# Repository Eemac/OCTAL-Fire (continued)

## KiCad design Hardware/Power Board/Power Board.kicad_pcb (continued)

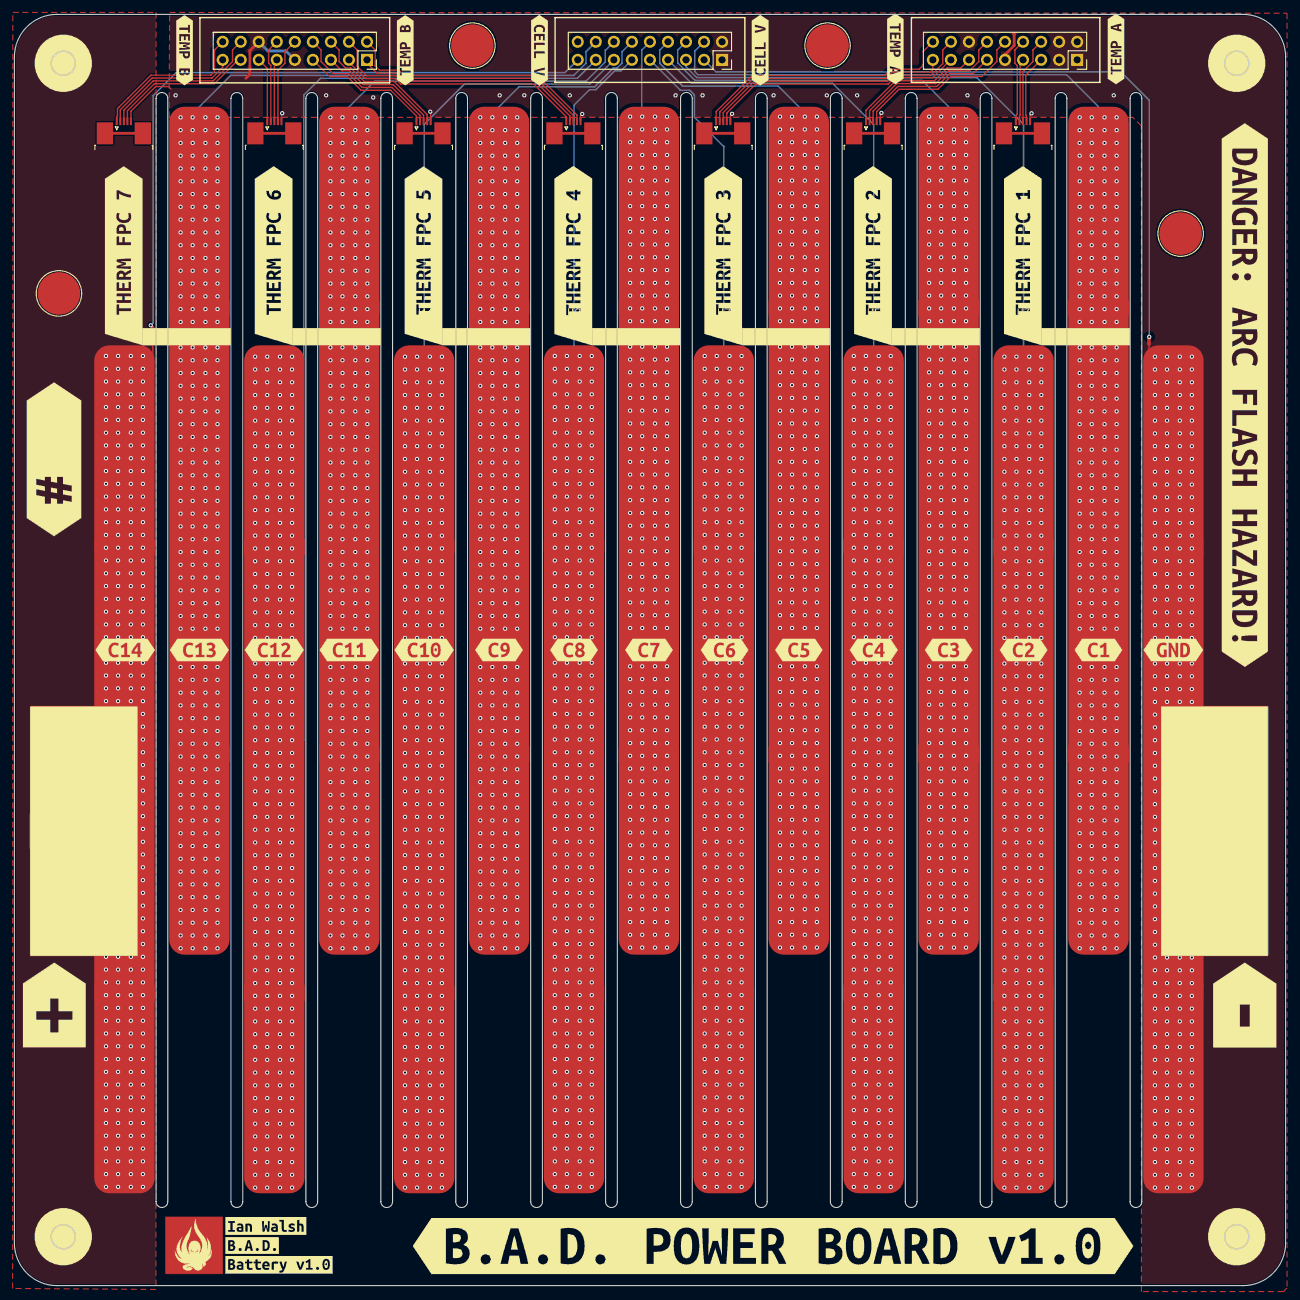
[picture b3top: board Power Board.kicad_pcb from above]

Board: 4 copper layers, 179.0 x 179.0 mm, 67 parts (0 on the bottom side), 45 nets.

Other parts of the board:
kibuzzard-68FE6C25: G***; kibuzzard-68FE6C25
kibuzzard-68FE8BAD: G***; kibuzzard-68FE8BAD
kibuzzard-68FE8C3A: G***; kibuzzard-68FE8C3A
kibuzzard-68FE8C6B: G***; kibuzzard-68FE8C6B
kibuzzard-68FE8C6F: G***; kibuzzard-68FE8C6F
kibuzzard-68FE8C7B: G***; kibuzzard-68FE8C7B
kibuzzard-68FE8C8C: G***; kibuzzard-68FE8C8C
kibuzzard-68FE8C9C: G***; kibuzzard-68FE8C9C
kibuzzard-68FE8C40: G***; kibuzzard-68FE8C40
kibuzzard-68FE8C46: G***; kibuzzard-68FE8C46
kibuzzard-68FE8C51: G***; kibuzzard-68FE8C51
kibuzzard-68FE8C58: G***; kibuzzard-68FE8C58
kibuzzard-68FE8C80: G***; kibuzzard-68FE8C80
kibuzzard-68FE8C86: G***; kibuzzard-68FE8C86
kibuzzard-68FE8C91: G***; kibuzzard-68FE8C91
kibuzzard-68FE8C96: G***; kibuzzard-68FE8C96
kibuzzard-68FE971D: G***; kibuzzard-68FE971D
kibuzzard-68FE972D: G***; kibuzzard-68FE972D
kibuzzard-68FE9722: G***; kibuzzard-68FE9722
kibuzzard-68FE9727: G***; kibuzzard-68FE9727
kibuzzard-68FE9731: G***; kibuzzard-68FE9731
kibuzzard-68FE9739: G***; kibuzzard-68FE9739
kibuzzard-69080D2C, kibuzzard-69080D2C#2: G***; kibuzzard-69080D2C
kibuzzard-69080D5F: G***; kibuzzard-69080D5F
kibuzzard-69080D67: G***; kibuzzard-69080D67
kibuzzard-69080DC3: G***; kibuzzard-69080DC3
kibuzzard-69080DCA: G***; kibuzzard-69080DCA
kibuzzard-69081DDA: G***; kibuzzard-69081DDA
kibuzzard-69081DE1: G***; kibuzzard-69081DE1
kibuzzard-690804B6: G***; kibuzzard-690804B6
kibuzzard-690816F8: G***; kibuzzard-690816F8
kibuzzard-6908043A: G***; kibuzzard-6908043A
kibuzzard-69080430: G***; kibuzzard-69080430
kibuzzard-69080435: G***; kibuzzard-69080435
kibuzzard-69080668: G***; kibuzzard-69080668

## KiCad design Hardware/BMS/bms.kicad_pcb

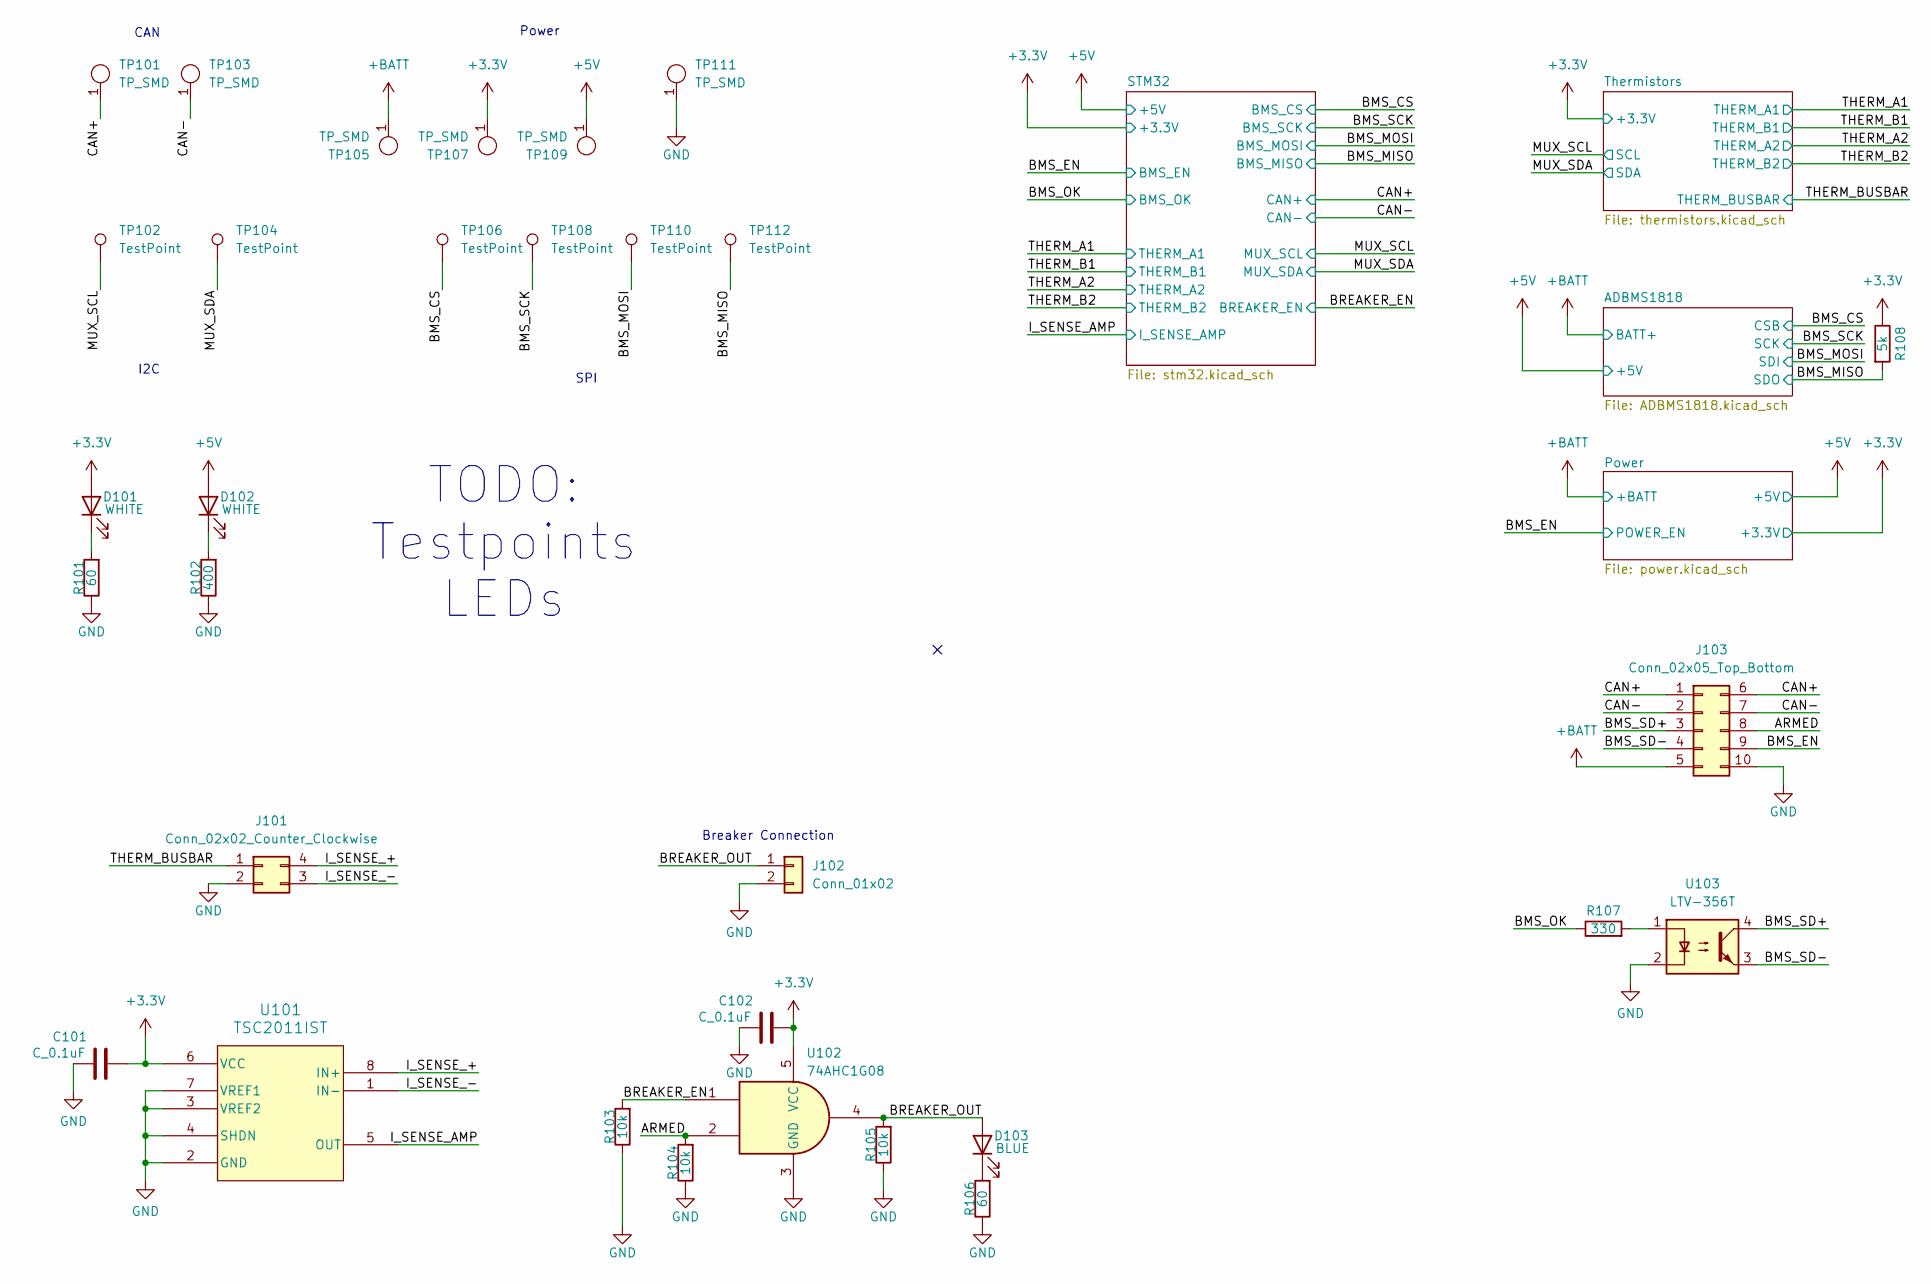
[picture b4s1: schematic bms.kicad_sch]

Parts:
C101, C102: C_0.1uF; C_0603_1608Metric; MPN 478-3352-1-ND
D101, D102: WHITE; LED_0805_2012Metric
D103: BLUE; LED_0805_2012Metric
J101: Conn_02x02_Counter_Clockwise; Molex_Micro-Fit_3.0_43045-0400_2x02_P3.00mm_Horizontal
J102: Conn_01x02; Molex_Micro-Fit_3.0_43650-0200_1x02_P3.00mm_Horizontal
J103: Conn_02x05_Top_Bottom; Molex_Micro-Fit_3.0_43045-1000_2x05_P3.00mm_Horizontal
R101, R106: 60; R_0603_1608Metric
R102: 400; R_0603_1608Metric
R103, R104, R105: 10k; R_0603_1608Metric
R107: 330; R_0603_1608Metric; MPN RMCF0603FT1K00
R108: 5k; R_0603_1608Metric; MPN RMCF0603FT1K00
TP101, TP103, TP105, TP107, TP109, TP111: TP_SMD; TestPoint_Keystone_5019_Miniature; MPN 5019
TP102, TP104, TP106, TP108, TP110, TP112: TestPoint; TestPoint_Pad_1.0x1.0mm
U101: TSC2011IST; SO_011IST_STM-M
U102: 74AHC1G08; SOT-23-5
U103: LTV-356T; SO-4_4.4x3.6mm_P2.54mm

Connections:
+3.3V: C101.2, C102.2, D101.2 (A), R108.1, TP107.1, U101.6 (VCC), U102.5 (VCC); also elsewhere on the board
+5V: D102.2 (A), TP109.1; also elsewhere on the board
/ARMED: J103.8, R104.2, U102.2
/BMS_CS: TP106.1; also elsewhere on the board
/BMS_EN: J103.9; also elsewhere on the board
/BMS_MISO: R108.2, TP112.1; also elsewhere on the board
/BMS_MOSI: TP110.1; also elsewhere on the board
/BMS_OK: R107.1; also elsewhere on the board
/BMS_SCK: TP108.1; also elsewhere on the board
/BMS_SD+: J103.3, U103.4
/BMS_SD-: J103.4, U103.3
/BREAKER_EN: R103.2, U102.1; also elsewhere on the board
/BREAKER_OUT: D103.2 (A), J102.1, R105.2, U102.4
/CAN+: J103.1, J103.6, TP101.1; also elsewhere on the board
/CAN-: J103.2, J103.7, TP103.1; also elsewhere on the board
/I_SENSE_+: J101.4, U101.8 (IN+)
/I_SENSE_-: J101.3, U101.1 (IN-)
/I_SENSE_AMP: U101.5 (OUT); also elsewhere on the board
/MUX_SCL: TP102.1; also elsewhere on the board
/MUX_SDA: TP104.1; also elsewhere on the board
/THERM_BUSBAR: J101.1; also elsewhere on the board
GND: C101.1, C102.1, J101.2, J102.2, J103.10, R101.1, R102.1, R103.1, R104.1, R105.1, R106.1, TP111.1, U101.2 (GND), U101.3 (VREF2), U101.4 (SHDN), U101.7 (VREF1), U102.3 (GND), U103.2; also elsewhere on the board
unnamed: D101.1 (K), R101.2
unnamed: D102.1 (K), R102.2
unnamed: D103.1 (K), R106.2
unnamed: R107.2, U103.1

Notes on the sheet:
I2C
CAN
TODO: Testpoints LEDs
SPI
Breaker Connection
Power

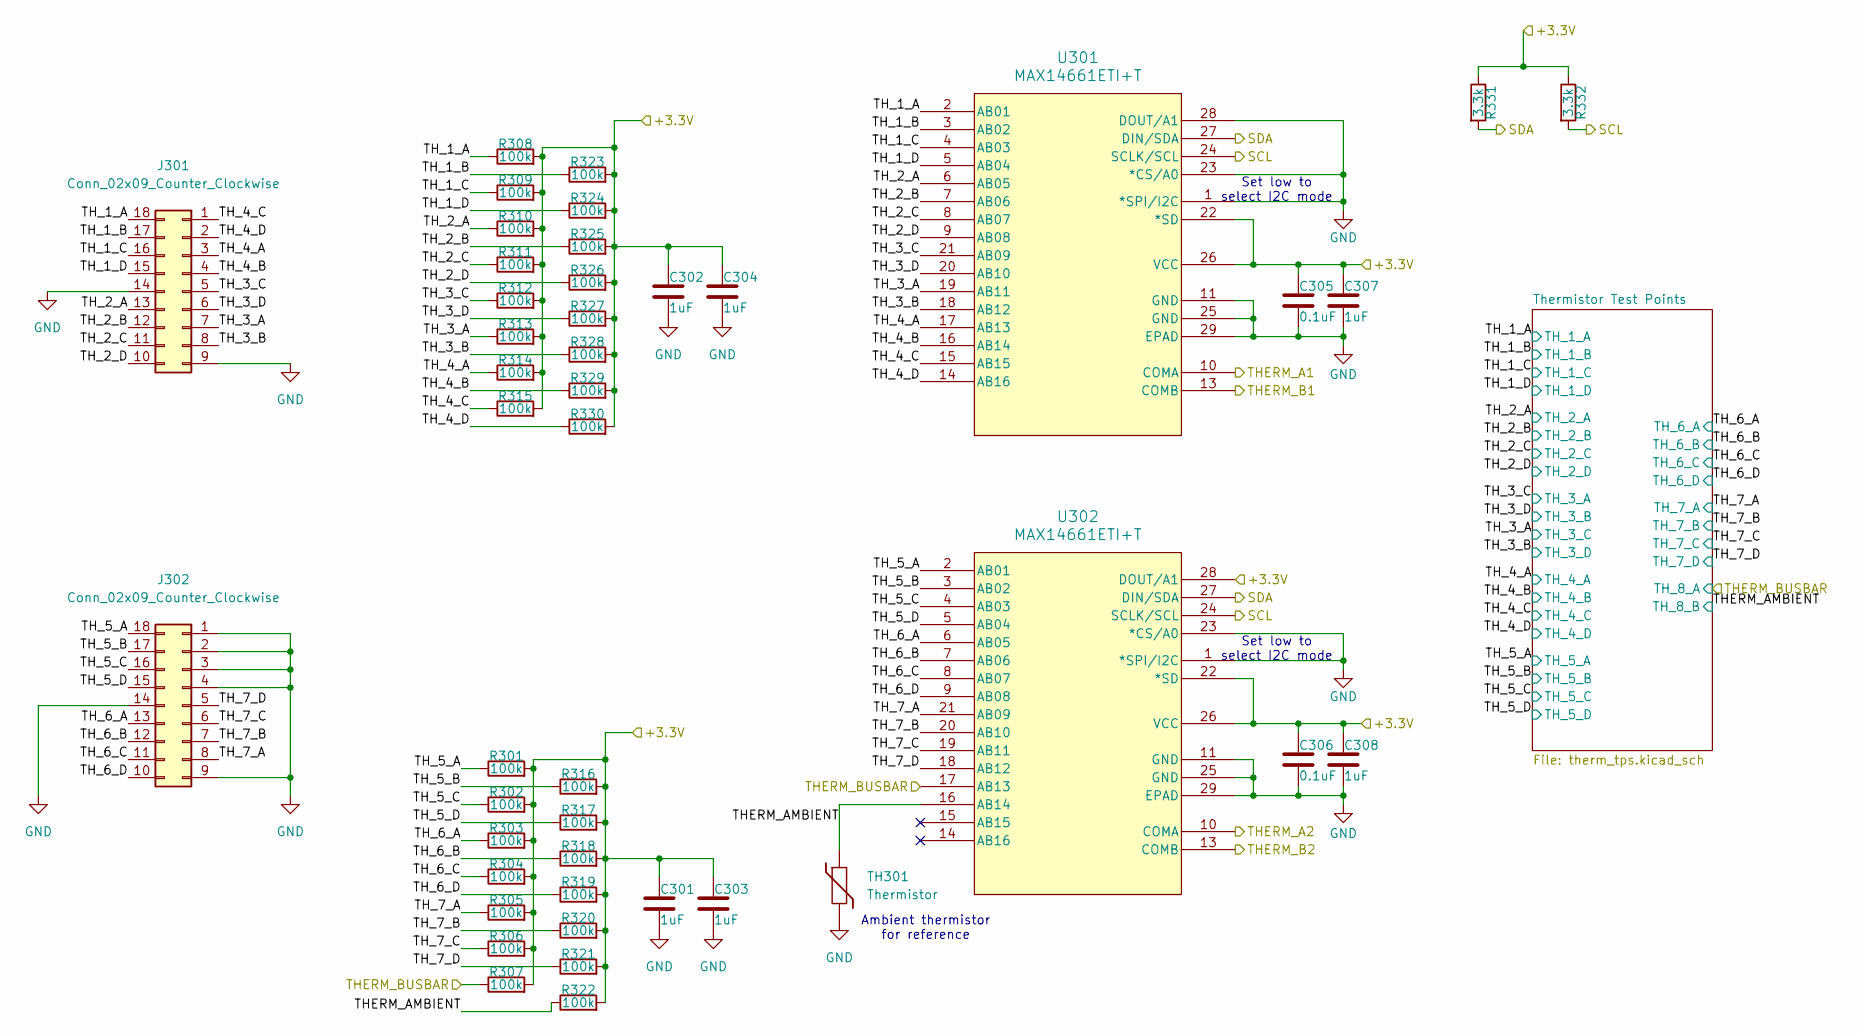
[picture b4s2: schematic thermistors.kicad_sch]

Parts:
C301, C302, C303, C304, C307, C308: 1uF; C_0603_1608Metric
C305, C306: 0.1uF; C_0603_1608Metric
J301, J302: Conn_02x09_Counter_Clockwise; PinSocket_2x09_P2.54mm_Vertical
R301, R302, R303, R304, R305, R306, R307, R308, R309, R310, R311, R312, R313, R314, R315, R316, R317, R318, R319, R320, R321, R322, R323, R324, R325, R326, R327, R328, R329, R330: 100k; R_0603_1608Metric
R331, R332: 3.3k; R_0603_1608Metric
TH301: Thermistor; R_0603_1608Metric
U301, U302: MAX14661ETI+T; 21-0139I_T2844-1_MXM

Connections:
+3.3V: C301.1, C302.1, C303.1, C304.1, C305.1, C306.1, C307.1, C308.1, R301.2, R302.2, R303.2, R304.2, R305.2, R306.2, R307.2, R308.2, R309.2, R310.2, R311.2, R312.2, R313.2, R314.2, R315.2, R316.2, R317.2, R318.2, R319.2, R320.2, R321.2, R322.2, R323.2, R324.2, R325.2, R326.2, R327.2, R328.2, R329.2, R330.2, R331.1, R332.1, U301.22 (*SD), U301.26 (VCC), U302.22 (*SD), U302.26 (VCC), U302.28 (DOUT/A1); also elsewhere on the board
/MUX_SCL: R332.2, U301.24 (SCLK/SCL), U302.24 (SCLK/SCL); also elsewhere on the board
/MUX_SDA: R331.2, U301.27 (DIN/SDA), U302.27 (DIN/SDA); also elsewhere on the board
/THERM_A1: U301.10 (COMA); also elsewhere on the board
/THERM_A2: U302.10 (COMA); also elsewhere on the board
/THERM_B1: U301.13 (COMB); also elsewhere on the board
/THERM_B2: U302.13 (COMB); also elsewhere on the board
/THERM_BUSBAR: R307.1, U302.17 (AB13); also elsewhere on the board
/Thermistors/THERM_AMBIENT: R322.1, TH301.1, U302.16 (AB14); also elsewhere on the board
/Thermistors/TH_1_A: J301.18, R308.1, U301.2 (AB01); also elsewhere on the board
/Thermistors/TH_1_B: J301.17, R323.1, U301.3 (AB02); also elsewhere on the board
/Thermistors/TH_1_C: J301.16, R309.1, U301.4 (AB03); also elsewhere on the board
/Thermistors/TH_1_D: J301.15, R324.1, U301.5 (AB04); also elsewhere on the board
/Thermistors/TH_2_A: J301.13, R310.1, U301.6 (AB05); also elsewhere on the board
/Thermistors/TH_2_B: J301.12, R325.1, U301.7 (AB06); also elsewhere on the board
/Thermistors/TH_2_C: J301.11, R311.1, U301.8 (AB07); also elsewhere on the board
/Thermistors/TH_2_D: J301.10, R326.1, U301.9 (AB08); also elsewhere on the board
/Thermistors/TH_3_A: J301.7, R313.1, U301.19 (AB11); also elsewhere on the board
/Thermistors/TH_3_B: J301.8, R328.1, U301.18 (AB12); also elsewhere on the board
/Thermistors/TH_3_C: J301.5, R312.1, U301.21 (AB09); also elsewhere on the board
/Thermistors/TH_3_D: J301.6, R327.1, U301.20 (AB10); also elsewhere on the board
/Thermistors/TH_4_A: J301.3, R314.1, U301.17 (AB13); also elsewhere on the board
/Thermistors/TH_4_B: J301.4, R329.1, U301.16 (AB14); also elsewhere on the board
/Thermistors/TH_4_C: J301.1, R315.1, U301.15 (AB15); also elsewhere on the board
/Thermistors/TH_4_D: J301.2, R330.1, U301.14 (AB16); also elsewhere on the board
/Thermistors/TH_5_A: J302.18, R301.1, U302.2 (AB01); also elsewhere on the board
/Thermistors/TH_5_B: J302.17, R316.1, U302.3 (AB02); also elsewhere on the board
/Thermistors/TH_5_C: J302.16, R302.1, U302.4 (AB03); also elsewhere on the board
/Thermistors/TH_5_D: J302.15, R317.1, U302.5 (AB04); also elsewhere on the board
/Thermistors/TH_6_A: J302.13, R303.1, U302.6 (AB05); also elsewhere on the board
/Thermistors/TH_6_B: J302.12, R318.1, U302.7 (AB06); also elsewhere on the board
/Thermistors/TH_6_C: J302.11, R304.1, U302.8 (AB07); also elsewhere on the board
/Thermistors/TH_6_D: J302.10, R319.1, U302.9 (AB08); also elsewhere on the board
GND: C301.2, C302.2, C303.2, C304.2, C305.2, C306.2, C307.2, C308.2, J301.9, J301.14, J302.1, J302.2, J302.3, J302.4, J302.9, J302.14, TH301.2, U301.1 (*SPI/I2C), U301.11 (GND), U301.23 (*CS/A0), U301.25 (GND), U301.28 (DOUT/A1), U301.29 (EPAD), U302.1 (*SPI/I2C), U302.11 (GND), U302.23 (*CS/A0), U302.25 (GND), U302.29 (EPAD); also elsewhere on the board

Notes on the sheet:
Set low to select I2C mode
Ambient thermistor for reference

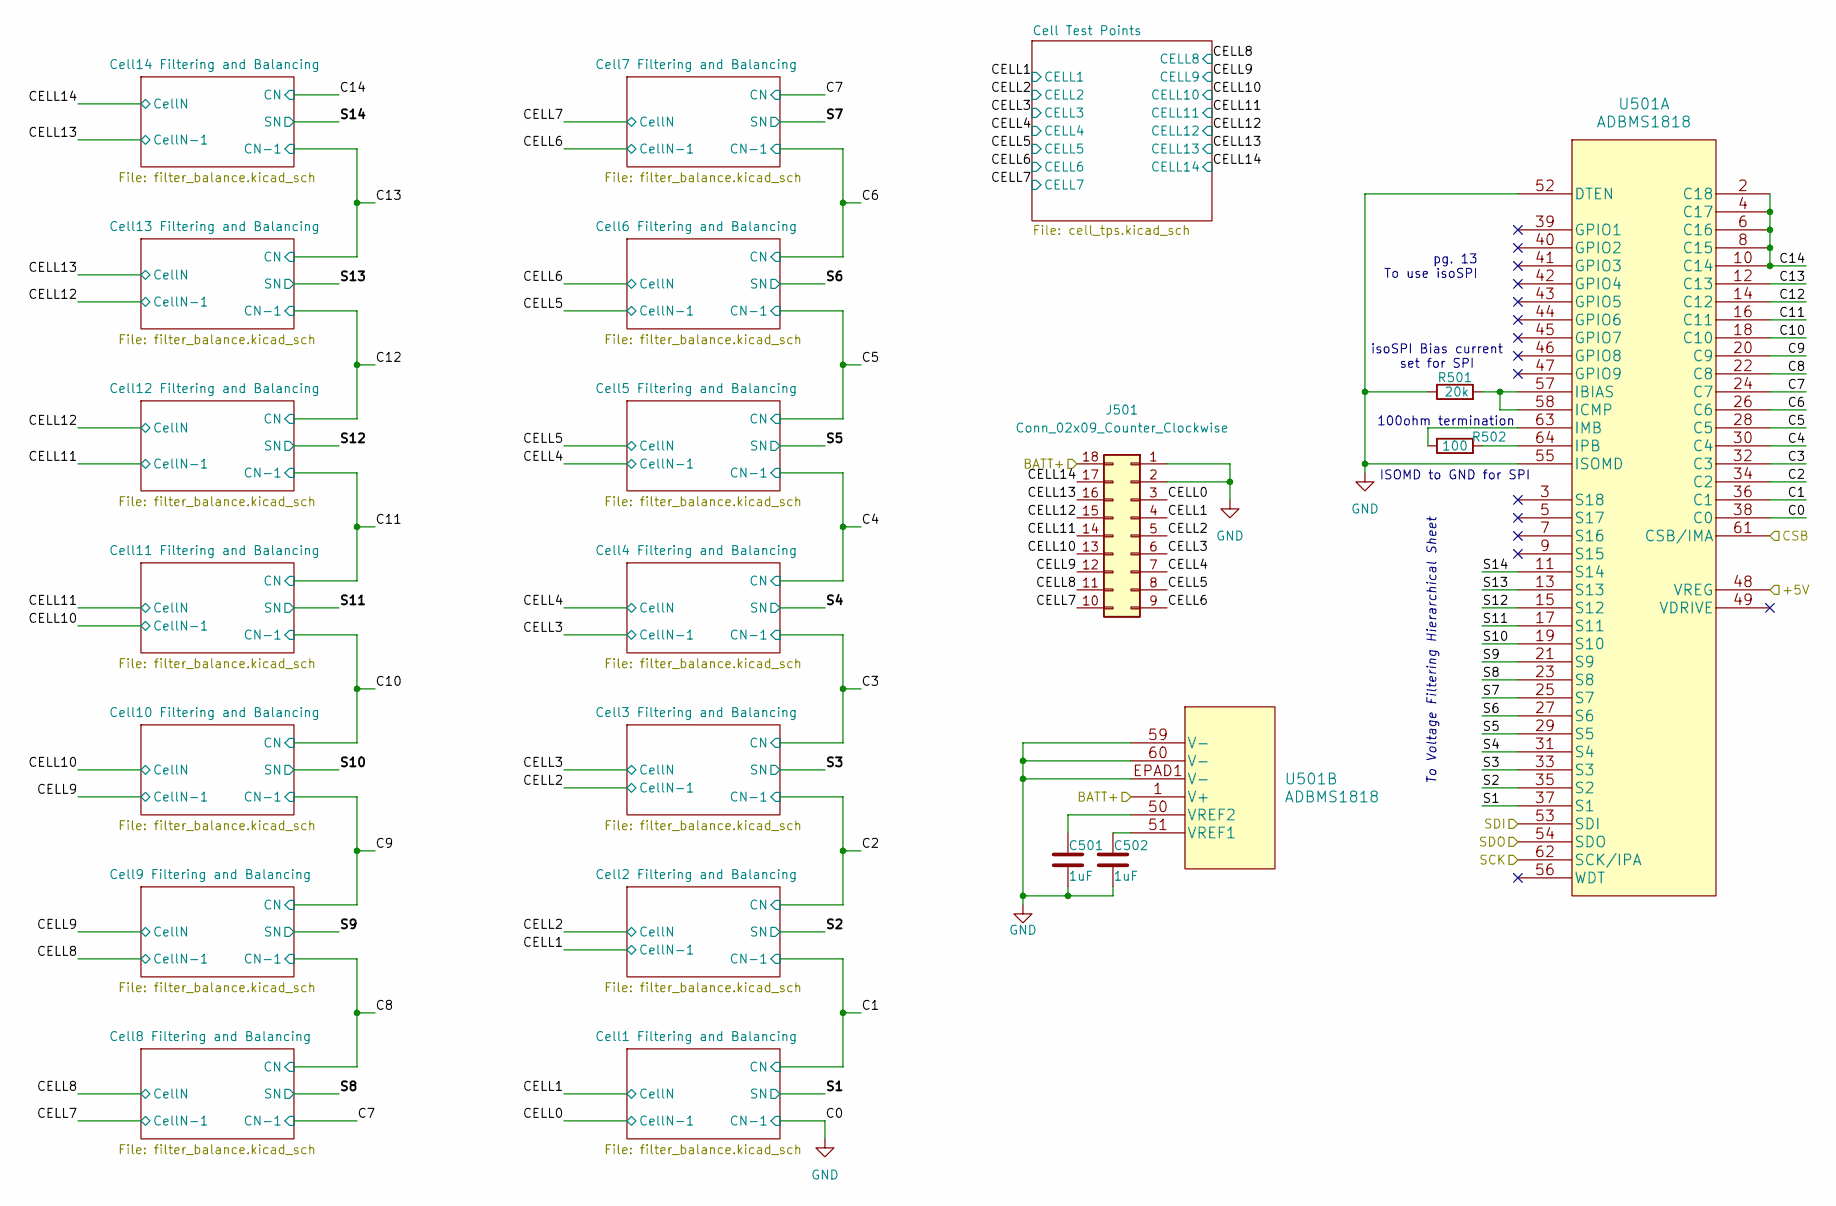
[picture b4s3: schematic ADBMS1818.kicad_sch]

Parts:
C501, C502: 1uF; C_0603_1608Metric
J501: Conn_02x09_Counter_Clockwise; PinSocket_2x09_P2.54mm_Vertical
R501: 20k; R_0603_1608Metric; MPN RMCF0603FT1K00
R502: 100; R_0603_1608Metric; MPN RMCF0603FT1K00
U501: ADBMS1818; LQFP-64-1EP_12x12_P0.5

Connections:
+5V: U501.48 (VREG); also elsewhere on the board
/ADBMS1818/C1: J501.4, U501.36 (C1); also elsewhere on the board
/ADBMS1818/C2: J501.5, U501.34 (C2); also elsewhere on the board
/ADBMS1818/C3: J501.6, U501.32 (C3); also elsewhere on the board
/ADBMS1818/C4: J501.7, U501.30 (C4); also elsewhere on the board
/ADBMS1818/C5: J501.8, U501.28 (C5); also elsewhere on the board
/ADBMS1818/C6: J501.9, U501.26 (C6); also elsewhere on the board
/ADBMS1818/C7: J501.10, U501.24 (C7); also elsewhere on the board
/ADBMS1818/C8: J501.11, U501.22 (C8); also elsewhere on the board
/ADBMS1818/C9: J501.12, U501.20 (C9); also elsewhere on the board
/ADBMS1818/C10: J501.13, U501.18 (C10); also elsewhere on the board
/ADBMS1818/C11: J501.14, U501.16 (C11); also elsewhere on the board
/ADBMS1818/C12: J501.15, U501.14 (C12); also elsewhere on the board
/ADBMS1818/C13: J501.16, U501.12 (C13); also elsewhere on the board
/ADBMS1818/C14: U501.2 (C18), U501.4 (C17), U501.6 (C16), U501.8 (C15), U501.10 (C14); also elsewhere on the board
/ADBMS1818/CELL14: J501.17; also elsewhere on the board
/ADBMS1818/S1: U501.37 (S1); also elsewhere on the board
/ADBMS1818/S2: U501.35 (S2); also elsewhere on the board
/ADBMS1818/S3: U501.33 (S3); also elsewhere on the board
/ADBMS1818/S4: U501.31 (S4); also elsewhere on the board
/ADBMS1818/S5: U501.29 (S5); also elsewhere on the board
/ADBMS1818/S6: U501.27 (S6); also elsewhere on the board
/ADBMS1818/S7: U501.25 (S7); also elsewhere on the board
/ADBMS1818/S8: U501.23 (S8); also elsewhere on the board
/ADBMS1818/S9: U501.21 (S9); also elsewhere on the board
/ADBMS1818/S10: U501.19 (S10); also elsewhere on the board
/ADBMS1818/S11: U501.17 (S11); also elsewhere on the board
/ADBMS1818/S12: U501.15 (S12); also elsewhere on the board
/ADBMS1818/S13: U501.13 (S13); also elsewhere on the board
/ADBMS1818/S14: U501.11 (S14); also elsewhere on the board
/BMS_CS: U501.61 (CSB/IMA); also elsewhere on the board
/BMS_MISO: U501.54 (SDO); also elsewhere on the board
/BMS_MOSI: U501.53 (SDI); also elsewhere on the board
/BMS_SCK: U501.62 (SCK/IPA); also elsewhere on the board
GND: C501.2, C502.2, J501.1, J501.2, J501.3, R501.1, U501.38 (C0), U501.52 (DTEN), U501.55 (ISOMD), U501.59 (V-), U501.60 (V-), U501.EPAD1 (V-); also elsewhere on the board
unnamed: R501.2, U501.57 (IBIAS), U501.58 (ICMP)
unnamed: R502.1, U501.63 (IMB)
unnamed: R502.2, U501.64 (IPB)
unnamed: C502.1, U501.51 (VREF1)
unnamed: C501.1, U501.50 (VREF2)

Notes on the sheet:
100ohm termination
pg. 13 To use isoSPI
ISOMD to GND for SPI
isoSPI Bias current set for SPI
To Voltage Filtering Hierarchical Sheet

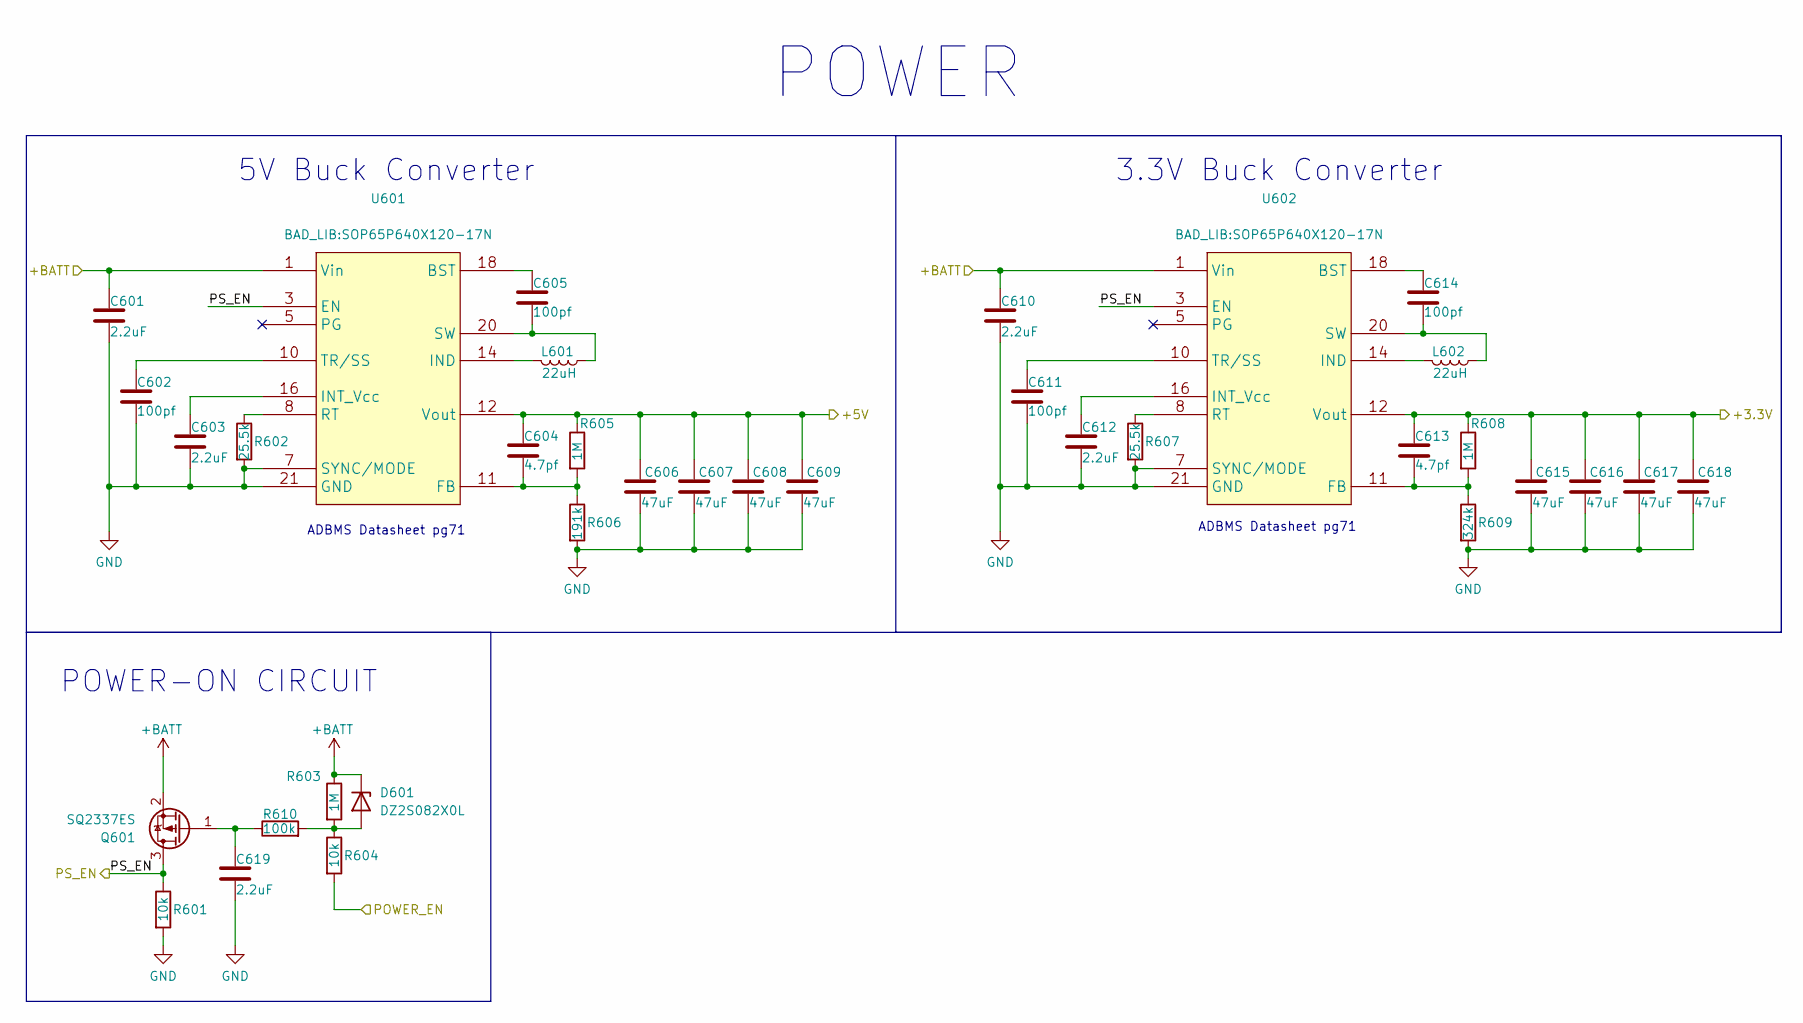
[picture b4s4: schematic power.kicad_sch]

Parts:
C601, C603, C610, C612, C619: 2.2uF; C_0603_1608Metric
C602, C605, C611, C614: 100pf; C_0603_1608Metric
C604, C613: 4.7pf; C_0603_1608Metric
C606, C607, C608, C609, C615, C616, C617, C618: 47uF; C_1206_3216Metric
D601: DZ2S082X0L; D_SOD-523
L601, L602: 22uH; L_12x12mm_H4.5mm
Q601: SQ2337ES; SOT-23
R601, R604: 10k; R_0603_1608Metric
R602, R607: 25.5k; R_0603_1608Metric
R603, R605, R608: 1M; R_0603_1608Metric
R606: 191k; R_0603_1608Metric
R609: 324k; R_0603_1608Metric
R610: 100k; R_0603_1608Metric
U601, U602: SOP65P640X120-17N

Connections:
+3.3V: C613.1, C615.1, C616.1, C617.1, C618.1, R608.1, U602.12 (Vout); also elsewhere on the board
+5V: C604.1, C606.1, C607.1, C608.1, C609.1, R605.1, U601.12 (Vout); also elsewhere on the board
/BMS_EN: R604.2; also elsewhere on the board
GND: C601.2, C602.2, C603.2, C606.2, C607.2, C608.2, C609.2, C610.2, C611.2, C612.2, C615.2, C616.2, C617.2, C618.2, C619.2, R601.2, R602.2, R606.2, R607.2, R609.2, U601.7 (SYNC/MODE), U601.21 (GND), U602.7 (SYNC/MODE), U602.21 (GND); also elsewhere on the board
unnamed: C605.1, U601.18 (BST)
unnamed: C604.2, R605.2, R606.1, U601.11 (FB)
unnamed: L601.2, U601.14 (IND)
unnamed: C603.1, U601.16 (INT_Vcc)
unnamed: R602.1, U601.8 (RT)
unnamed: C605.2, L601.1, U601.20 (SW)
unnamed: C602.1, U601.10 (TR/SS)
unnamed: C614.1, U602.18 (BST)
unnamed: C613.2, R608.2, R609.1, U602.11 (FB)
unnamed: L602.2, U602.14 (IND)
unnamed: C612.1, U602.16 (INT_Vcc)
unnamed: R607.1, U602.8 (RT)
unnamed: C614.2, L602.1, U602.20 (SW)
unnamed: C611.1, U602.10 (TR/SS)

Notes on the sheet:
3.3V Buck Converter
ADBMS Datasheet pg71
POWER-ON CIRCUIT
5V Buck Converter
POWER

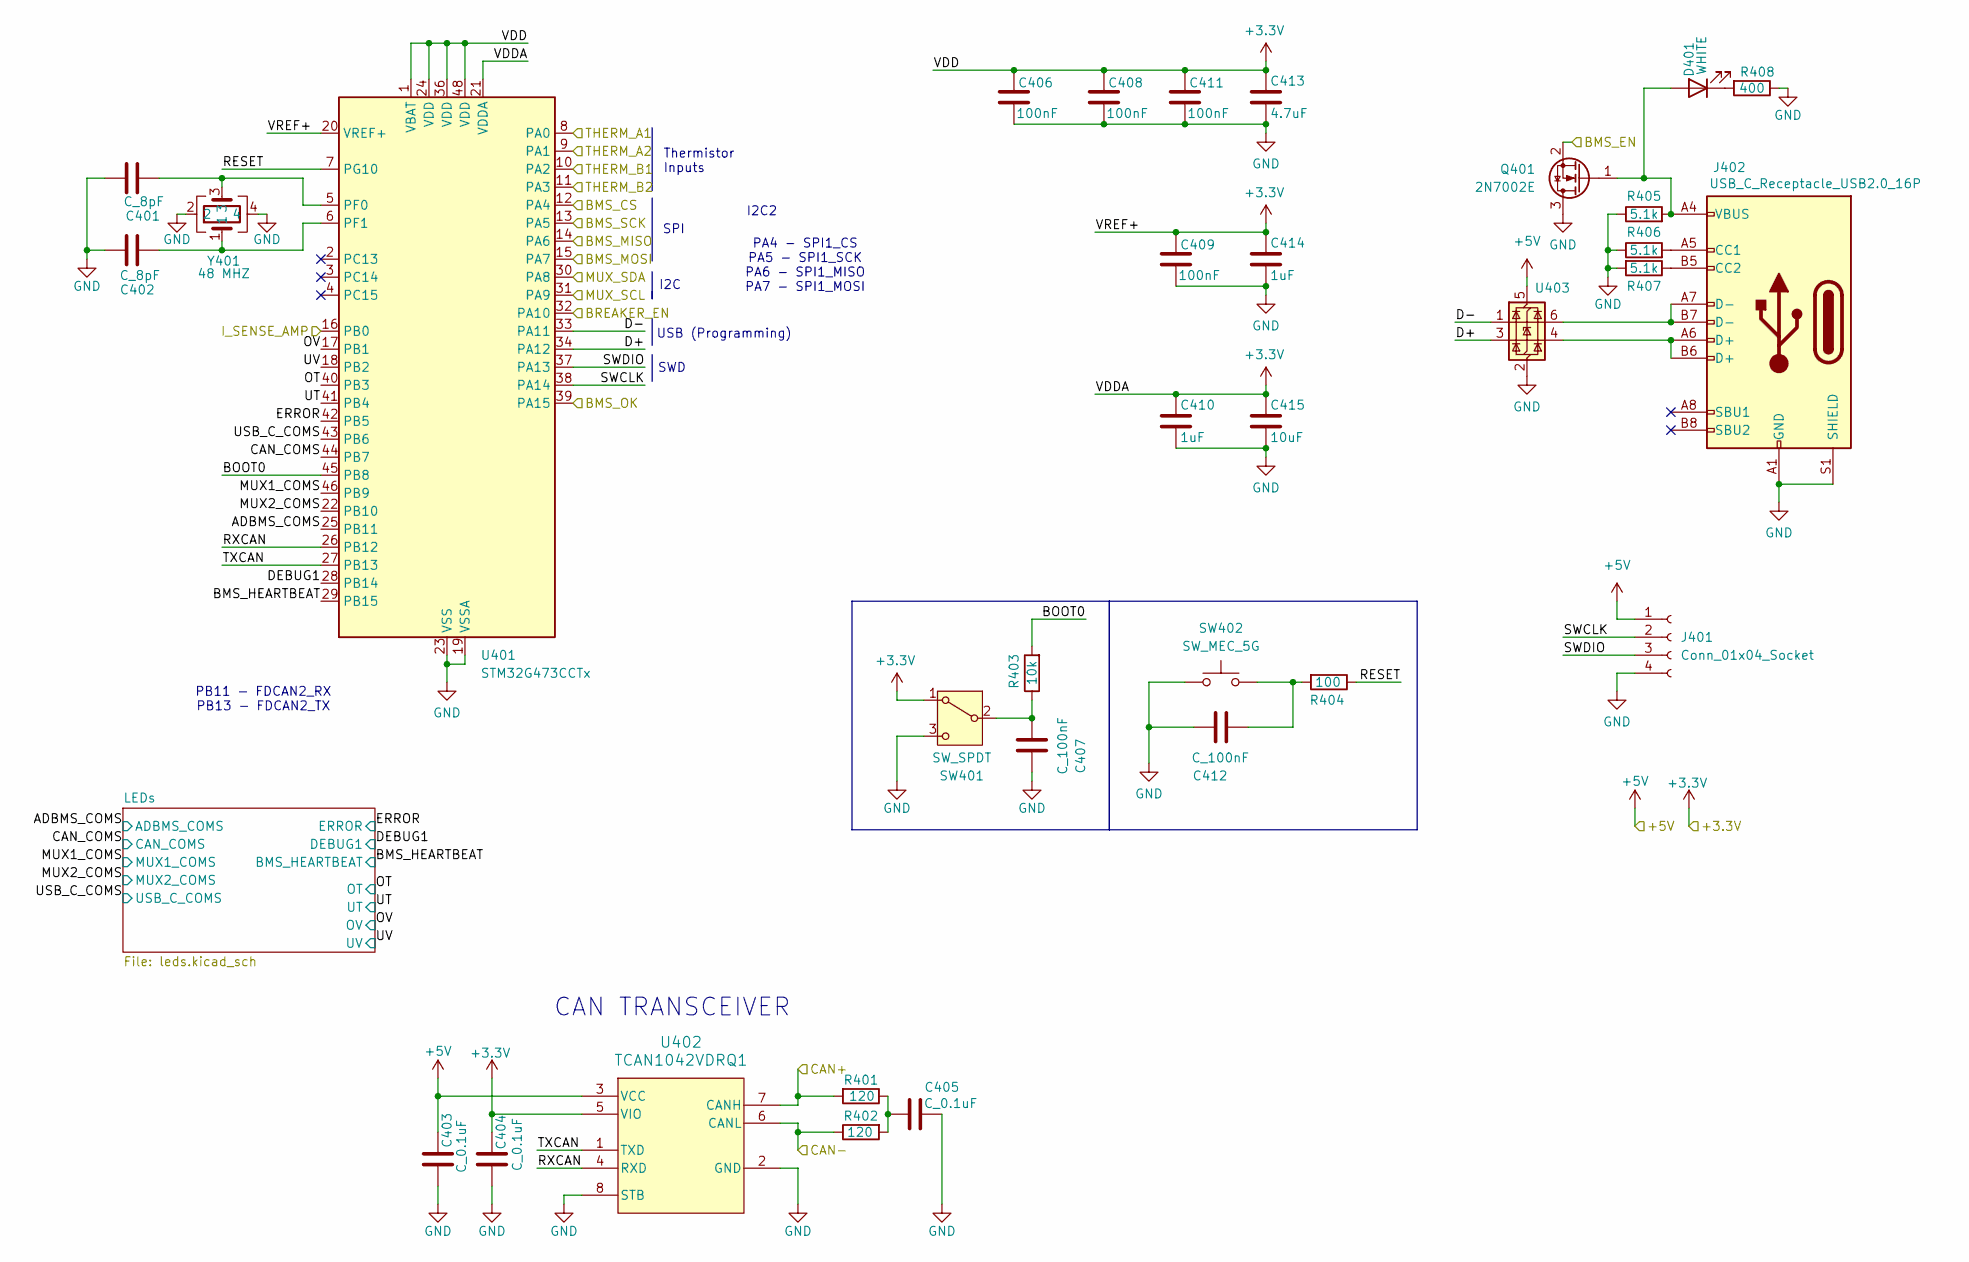
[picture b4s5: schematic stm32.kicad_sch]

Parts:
C401, C402: C_8pF; C_0603_1608Metric; MPN 1276-6717-1-ND
C403, C404, C405: C_0.1uF; C_0603_1608Metric; MPN 478-3352-1-ND
C406, C408, C409, C411: 100nF; C_0603_1608Metric; MPN 1276-6717-1-ND
C407, C412: C_100nF; C_0603_1608Metric; MPN 1276-6717-1-ND
C410, C414: 1uF; C_0603_1608Metric; MPN 1276-1052-1-ND
C413: 4.7uF; C_0805_2012Metric; MPN 1276-1052-1-ND
C415: 10uF; C_0805_2012Metric; MPN 1276-1052-1-ND
D401: WHITE; LED_0805_2012Metric
J401: Conn_01x04_Socket; PinSocket_1x04_P2.54mm_Vertical
J402: USB_C_Receptacle_USB2.0_16P; USB_C_Receptacle_G-Switch_GT-USB-7051x
Q401: 2N7002E; SOT-23
R401, R402: 120; R_0603_1608Metric; MPN 667-ERJ-6ENF1200V
R403: 10k; R_0805_OEM; MPN CRS0805-FX-1002ELFCT-ND
R404: 100; R_0805_OEM; MPN CRS0805-FX-1002ELFCT-ND
R405, R406, R407: 5.1k; R_0603_1608Metric; MPN RMCF0603FT1K00
R408: 400; R_0603_1608Metric
SW401: SW_SPDT; SW_SPDT_Shouhan_MSK12C02
SW402: SW_MEC_5G; SW_MEC_5GSH9
U401: STM32G473CCTx; LQFP-48_7x7mm_P0.5mm
U402: TCAN1042VDRQ1; D0008A_M
U403: USBLC6-2SC6; SOT-23-6
Y401: 48 MHZ; Crystal_SMD_FA238; MPN 7M48072002

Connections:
+3.3V: C404.1, C406.1, C408.1, C409.1, C410.1, C411.1, C413.1, C414.1, C415.1, SW401.1 (A), U401.1 (VBAT), U401.20 (VREF+), U401.21 (VDDA), U401.24 (VDD), U401.36 (VDD), U401.48 (VDD), U402.5 (VIO); also elsewhere on the board
+5V: C403.1, J401.1, U402.3 (VCC), U403.5 (VBUS); also elsewhere on the board
/BMS_CS: U401.12 (PA4); also elsewhere on the board
/BMS_EN: Q401.2 (S); also elsewhere on the board
/BMS_MISO: U401.14 (PA6); also elsewhere on the board
/BMS_MOSI: U401.15 (PA7); also elsewhere on the board
/BMS_OK: U401.39 (PA15); also elsewhere on the board
/BMS_SCK: U401.13 (PA5); also elsewhere on the board
/BREAKER_EN: U401.32 (PA10); also elsewhere on the board
/CAN+: R401.2, U402.7 (CANH); also elsewhere on the board
/CAN-: R402.1, U402.6 (CANL); also elsewhere on the board
/I_SENSE_AMP: U401.16 (PB0); also elsewhere on the board
/MUX_SCL: U401.31 (PA9); also elsewhere on the board
/MUX_SDA: U401.30 (PA8); also elsewhere on the board
/STM32/ADBMS_COMS: U401.25 (PB11); also elsewhere on the board
/STM32/BMS_HEARTBEAT: U401.29 (PB15); also elsewhere on the board
/STM32/BOOT0: R403.2, U401.45 (PB8)
/STM32/CAN_COMS: U401.44 (PB7); also elsewhere on the board
/STM32/D+: U401.34 (PA12), U403.3 (I/O2)
/STM32/D-: U401.33 (PA11), U403.1 (I/O1)
/STM32/DEBUG1: U401.28 (PB14); also elsewhere on the board
/STM32/ERROR: U401.42 (PB5); also elsewhere on the board
/STM32/MUX1_COMS: U401.46 (PB9); also elsewhere on the board
/STM32/MUX2_COMS: U401.22 (PB10); also elsewhere on the board
/STM32/OT: U401.40 (PB3); also elsewhere on the board
/STM32/OV: U401.17 (PB1); also elsewhere on the board
/STM32/RESET: R404.1, U401.7 (PG10)
/STM32/RXCAN: U401.26 (PB12), U402.4 (RXD)
/STM32/SWCLK: J401.2, U401.38 (PA14)
/STM32/SWDIO: J401.3, U401.37 (PA13)
/STM32/TXCAN: U401.27 (PB13), U402.1 (TXD)
/STM32/USB_C_COMS: U401.43 (PB6); also elsewhere on the board
/STM32/UT: U401.41 (PB4); also elsewhere on the board
/STM32/UV: U401.18 (PB2); also elsewhere on the board
/THERM_A1: U401.8 (PA0); also elsewhere on the board
/THERM_A2: U401.9 (PA1); also elsewhere on the board
/THERM_B1: U401.10 (PA2); also elsewhere on the board
/THERM_B2: U401.11 (PA3); also elsewhere on the board
GND: C401.2, C402.1, C403.2, C404.2, C405.2, C406.2, C407.1, C408.2, C409.2, C410.2, C411.2, C412.1, C413.2, C414.2, C415.2, J401.4, J402.A1 (GND), J402.A12 (GND), J402.B1 (GND), J402.B12 (GND), J402.S1 (SHIELD), Q401.3 (D), R405.1, R406.1, R407.2, R408.1, SW401.3 (C), SW402.1 (A), SW402.2 (A), U401.19 (VSSA), U401.23 (VSS), U401.35 (VSS), U401.47 (VSS), U402.2 (GND), U402.8 (STB), U403.2 (GND), Y401.2, Y401.4; also elsewhere on the board
unnamed: C405.1, R401.1, R402.2
unnamed: C412.2, R404.2, SW402.3 (B), SW402.4 (B)
unnamed: D401.2 (A), J402.A4 (VBUS), J402.A9 (VBUS), J402.B4 (VBUS), J402.B9 (VBUS), Q401.1 (G), R405.2
unnamed: D401.1 (K), R408.2
unnamed: J402.A5 (CC1), R406.2
unnamed: J402.B5 (CC2), R407.1
unnamed: J402.A6 (D+), J402.B6 (D+), U403.4 (I/O2)
unnamed: J402.A7 (D-), J402.B7 (D-), U403.6 (I/O1)
unnamed: C407.2, R403.1, SW401.2 (B)
unnamed: C401.1, U401.5 (PF0), Y401.3
unnamed: C402.2, U401.6 (PF1), Y401.1

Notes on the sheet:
I2C
PA4 - SPI1_CS PA5 - SPI1_SCK PA6 - SPI1_MISO PA7 - SPI1_MOSI
CAN TRANSCEIVER
SWD
SPI
USB (Programming)
I2C2
PB11 - FDCAN2_RX PB13 - FDCAN2_TX
Thermistor Inputs
